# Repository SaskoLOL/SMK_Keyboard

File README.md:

# SMK_Keyboard
This is a cool 119 key mechanical keyboard. It has 9 macro keys, 4 on top and 5 on the left. (Total time spent: 40h)

#CAD
I modeled everything in fusion 360

This is the full case

It consist of 2 parts:

PCB
The schmetick consists of 119 switches and diodes and uses a rasbarry pi pico (orpheus pico)

The PCB consists only of 2 layers:

UPDATED PICTURE (because I had the thing mirrored and it looked like the screw holes would go trough the pcb and top case)

UPDATE: made the usb space look alot better:

Firmware:
The firmware was made in VS code with Pyhton

BOM:

119 cherry mx switches cost: 52.80€ Required: Yes Link: https://www.reichelt.at/at/de/shop/produkt/cherry_mx_blue_-_tastenmodul_-_fixierzapfen-369269?PROVID=2807&gad_source=1&gad_campaignid=21422869099&gbraid=0AAAAADwnxtat6u9lsAHToV6GKxf7BibTs&gclid=CjwKCAjwvuLDBhAOEiwAPtF0VhZ3tHRP4ssGiYqpavdrLBmLvci3DstJQDXffXF_gPWklEFFPWfM4RoCDl0QAvD_BwE 

One orpheus pico: 10€ Required: No

M3x16mm screws (6x): 3€: Required: No

119 blank keycaps: 29,90 €: Required: Yes Link:https://www.caseking.de/ducky-blank-white-pbt-set-mda-profile-133-keycaps-ansi-us-layout-ansi-us-layout/GAKC-530.html?gad_source=1&gad_campaignid=21451873868&gbraid=0AAAAABRBl3rp2MxtPfOOeLMF1GxUSPO_i&gclid=CjwKCAjwvuLDBhAOEiwAPtF0Vpwwld4mDaxte3PK0Otz3Z-v6C9MTZain8aGXCld9Vo5LzLQT2UPhRoCZhEQAvD_BwE ALIEXPRESS LINK (updated): https://de.aliexpress.com/i/1005008530984427.html?gatewayAdapt=glo2deu Cost:21,07$

3d printing Filament: 20€ Required Yes

Pcb: / Required: Yes
Total cost: 130$

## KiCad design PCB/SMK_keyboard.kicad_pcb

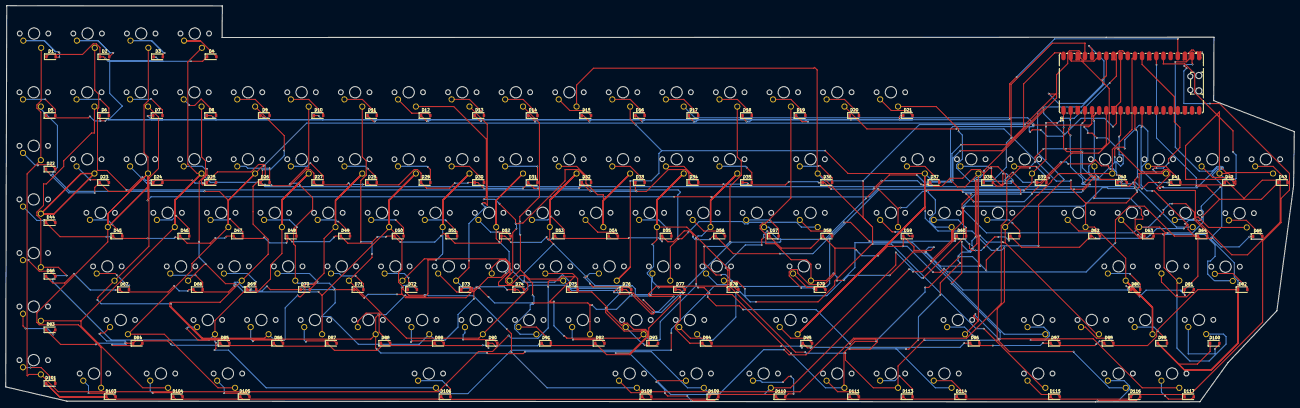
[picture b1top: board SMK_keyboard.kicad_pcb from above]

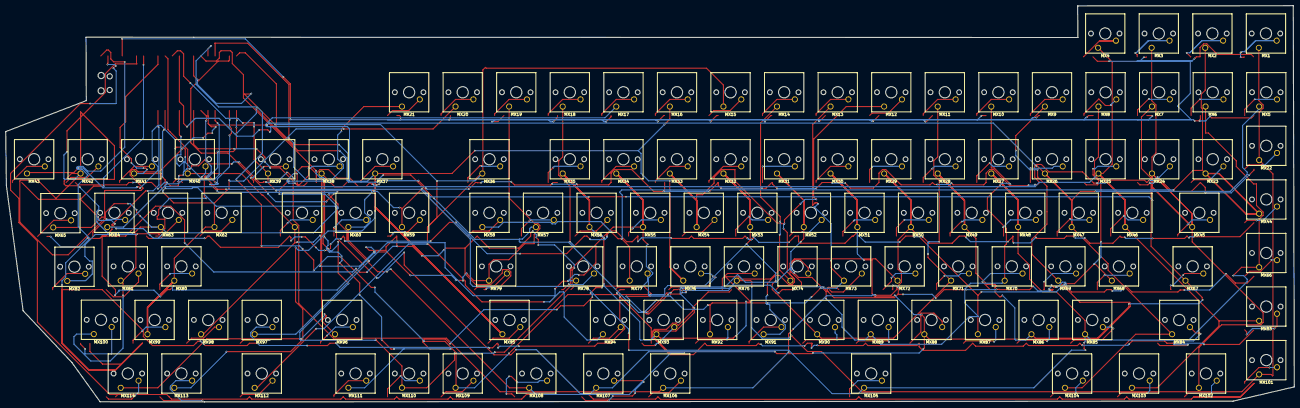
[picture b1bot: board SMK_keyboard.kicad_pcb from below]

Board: 2 copper layers, 458.2 x 140.9 mm, 229 parts (114 on the bottom side), 141 nets.

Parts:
D1, D2, D3, D4, D5, D6, D7, D8, D9, D10, D11, D12, D13, D14, D15, D16, D17, D18, D19, D20, D21, D22, D23, D24, D25, D26, D27, D28, D29, D30, D31, D32, D33, D34, D35, D36, D37, D38, D39, D40, D41, D42, D43, D44, D45, D46, D47, D48, D49, D50, D51, D52, D53, D54, D55, D56, D57, D58, D59, D60, D61, D62, D63, D64, D65, D66, D67, D68, D69, D70, D71, D72, D73, D74, D75, D76, D77, D78, D79, D80, D81, D82, D83, D84, D85, D86, D87, D88, D89, D90, D91, D92, D93, D94, D95, D96, D97, D98, D99, D100, D101, D103, D104, D105, D106, D108, D109, D110, D111, D113, D114, D115, D116, D117: D; D_SOD-123
MX1, MX2, MX3, MX4, MX5, MX6, MX7, MX8, MX9, MX10, MX11, MX12, MX13, MX14, MX15, MX16, MX17, MX18, MX19, MX20, MX21, MX22, MX23, MX24, MX25, MX26, MX27, MX28, MX29, MX30, MX31, MX32, MX33, MX34, MX35, MX36, MX37, MX38, MX39, MX40, MX41, MX42, MX43, MX44, MX45, MX46, MX47, MX48, MX49, MX50, MX51, MX52, MX53, MX54, MX55, MX56, MX57, MX58, MX59, MX60, MX61, MX62, MX63, MX64, MX65, MX66, MX67, MX68, MX69, MX70, MX71, MX72, MX73, MX74, MX75, MX76, MX77, MX78, MX79, MX80, MX81, MX82, MX83, MX84, MX85, MX86, MX87, MX88, MX89, MX90, MX91, MX92, MX93, MX94, MX95, MX96, MX97, MX98, MX99, MX100, MX101, MX102, MX103, MX104, MX105, MX106, MX107, MX108, MX109, MX110, MX111, MX112, MX113, MX114: MX_SW_HS; SW_Cherry_MX_1.00u_PCB
U1: Pico; RaspberryPi_Pico_Common_SMD

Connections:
unnamed: D1.2 (A), MX1.2
unnamed: D2.2 (A), MX2.2
unnamed: D3.2 (A), MX3.2
unnamed: D4.2 (A), MX4.2
unnamed: D5.2 (A), MX5.2
unnamed: D6.2 (A), MX6.2
unnamed: D7.2 (A), MX7.2
unnamed: D8.2 (A), MX8.2
unnamed: D9.2 (A), MX9.2
unnamed: D10.2 (A), MX10.2
unnamed: D11.2 (A), MX11.2
unnamed: D12.2 (A), MX12.2
unnamed: D13.2 (A), MX13.2
unnamed: D14.2 (A), MX14.2
unnamed: D15.2 (A), MX15.2
unnamed: D16.2 (A), MX16.2
unnamed: D17.2 (A), MX17.2
unnamed: D18.2 (A), MX18.2
unnamed: D19.2 (A), MX19.2
unnamed: D20.2 (A), MX20.2
unnamed: D21.2 (A), MX21.2
unnamed: D22.2 (A), MX22.2
unnamed: D23.2 (A), MX23.2
unnamed: D24.2 (A), MX24.2
unnamed: D25.2 (A), MX25.2
unnamed: D26.2 (A), MX26.2
unnamed: D27.2 (A), MX27.2
unnamed: D28.2 (A), MX28.2
unnamed: D29.2 (A), MX29.2
unnamed: D30.2 (A), MX30.2
unnamed: D31.2 (A), MX31.2
unnamed: D32.2 (A), MX32.2
unnamed: D33.2 (A), MX33.2
unnamed: D34.2 (A), MX34.2
unnamed: D35.2 (A), MX35.2
unnamed: D36.2 (A), MX36.2
unnamed: D37.2 (A), MX37.2
unnamed: D38.2 (A), MX38.2
unnamed: D39.2 (A), MX39.2
unnamed: D40.2 (A), MX40.2
unnamed: D41.2 (A), MX41.2
unnamed: D42.2 (A), MX42.2
unnamed: D43.2 (A), MX43.2
unnamed: D44.2 (A), MX44.2
unnamed: D45.2 (A), MX45.2
unnamed: D46.2 (A), MX46.2
unnamed: D47.2 (A), MX47.2
unnamed: D48.2 (A), MX48.2
unnamed: D49.2 (A), MX49.2
unnamed: D50.2 (A), MX50.2
unnamed: D51.2 (A), MX51.2
unnamed: D52.2 (A), MX52.2
unnamed: D53.2 (A), MX53.2
unnamed: D54.2 (A), MX54.2
unnamed: D55.2 (A), MX55.2
unnamed: D56.2 (A), MX56.2
unnamed: D57.2 (A), MX57.2
unnamed: D58.2 (A), MX58.2
unnamed: D59.2 (A), MX59.2
unnamed: D60.2 (A), MX60.2
unnamed: D61.2 (A), MX61.2
unnamed: D62.2 (A), MX62.2
unnamed: D63.2 (A), MX63.2
unnamed: D64.2 (A), MX64.2
unnamed: D65.2 (A), MX65.2
unnamed: D66.2 (A), MX66.2
unnamed: D67.2 (A), MX67.2
unnamed: D68.2 (A), MX68.2
unnamed: D69.2 (A), MX69.2
unnamed: D70.2 (A), MX70.2
unnamed: D71.2 (A), MX71.2
unnamed: D72.2 (A), MX72.2
unnamed: D73.2 (A), MX73.2
unnamed: D74.2 (A), MX74.2
unnamed: D75.2 (A), MX75.2
unnamed: D76.2 (A), MX76.2
unnamed: D77.2 (A), MX77.2
unnamed: D78.2 (A), MX78.2
unnamed: D79.2 (A), MX79.2
unnamed: D80.2 (A), MX80.2
unnamed: D81.2 (A), MX81.2
unnamed: D82.2 (A), MX82.2
unnamed: D83.2 (A), MX83.2
unnamed: D84.2 (A), MX84.2
unnamed: D85.2 (A), MX85.2
unnamed: D86.2 (A), MX86.2
unnamed: D87.2 (A), MX87.2
unnamed: D88.2 (A), MX88.2
unnamed: D89.2 (A), MX89.2
unnamed: D90.2 (A), MX90.2
unnamed: D91.2 (A), MX91.2
unnamed: D92.2 (A), MX92.2
unnamed: D93.2 (A), MX93.2
unnamed: D94.2 (A), MX94.2
unnamed: D95.2 (A), MX95.2
unnamed: D96.2 (A), MX96.2
unnamed: D97.2 (A), MX97.2
unnamed: D98.2 (A), MX98.2
unnamed: D99.2 (A), MX99.2
unnamed: D100.2 (A), MX100.2
unnamed: D101.2 (A), MX101.2
unnamed: D103.2 (A), MX102.2
unnamed: D104.2 (A), MX103.2
unnamed: D105.2 (A), MX104.2
unnamed: D106.2 (A), MX105.2
unnamed: D108.2 (A), MX106.2
unnamed: D109.2 (A), MX107.2
unnamed: D110.2 (A), MX108.2
unnamed: D111.2 (A), MX109.2
unnamed: D113.2 (A), MX110.2
unnamed: D114.2 (A), MX111.2
unnamed: D115.2 (A), MX112.2
unnamed: D116.2 (A), MX113.2
unnamed: D117.2 (A), MX114.2
unnamed: MX2.1, MX23.1, MX44.1, MX58.1, MX77.1
unnamed: MX12.1, MX33.1, MX54.1, MX72.1, MX91.1
unnamed: MX7.1, MX28.1, MX49.1, MX67.1, MX86.1
Row1: D75.1 (K), D77.1 (K), D82.1 (K), D83.1 (K), D84.1 (K), D85.1 (K), D86.1 (K), D87.1 (K), D88.1 (K), D89.1 (K), D90.1 (K), D91.1 (K), D92.1 (K), D93.1 (K), D94.1 (K), D95.1 (K), D96.1 (K), D97.1 (K), D98.1 (K), D99.1 (K), D100.1 (K), U1.1 (GPIO0)
Row2: D101.1 (K), D103.1 (K), D104.1 (K), D105.1 (K), D106.1 (K), D108.1 (K), D109.1 (K), D110.1 (K), D111.1 (K), D113.1 (K), D114.1 (K), D115.1 (K), D116.1 (K), D117.1 (K), U1.2 (GPIO1)
Row3: D1.1 (K), D2.1 (K), D3.1 (K), D4.1 (K), D5.1 (K), D6.1 (K), D7.1 (K), D8.1 (K), D9.1 (K), D10.1 (K), D11.1 (K), D12.1 (K), D13.1 (K), D14.1 (K), D15.1 (K), D16.1 (K), D17.1 (K), D18.1 (K), D19.1 (K), D20.1 (K), D21.1 (K), U1.4 (GPIO2)
Row4: D22.1 (K), D23.1 (K), D24.1 (K), D25.1 (K), D26.1 (K), D27.1 (K), D28.1 (K), D29.1 (K), D30.1 (K), D31.1 (K), D32.1 (K), D33.1 (K), D34.1 (K), D35.1 (K), D36.1 (K), D37.1 (K), D38.1 (K), D39.1 (K), D40.1 (K), D41.1 (K), D42.1 (K), U1.29 (GPIO22)
Row5: D43.1 (K), D44.1 (K), D45.1 (K), D46.1 (K), D47.1 (K), D48.1 (K), D49.1 (K), D50.1 (K), D51.1 (K), D52.1 (K), D53.1 (K), D54.1 (K), D55.1 (K), D56.1 (K), D60.1 (K), D61.1 (K), D62.1 (K), D63.1 (K), U1.7 (GPIO5)
Row6: D57.1 (K), D58.1 (K), D59.1 (K), D64.1 (K), D65.1 (K), D66.1 (K), D67.1 (K), D68.1 (K), D69.1 (K), D70.1 (K), D71.1 (K), D72.1 (K), D73.1 (K), D74.1 (K), D76.1 (K), D78.1 (K), D79.1 (K), D80.1 (K), D81.1 (K), U1.32 (GPIO27_ADC1)
col0: MX1.1, MX22.1, MX43.1, MX57.1, MX75.1, MX101.1, U1.21 (GPIO16)
col1: MX3.1, MX24.1, MX45.1, MX59.1, MX82.1, MX102.1, U1.22 (GPIO17)
col2: MX4.1, MX25.1, MX46.1, MX64.1, MX83.1, MX103.1, U1.24 (GPIO18)
col3: MX5.1, MX26.1, MX47.1, MX65.1, MX84.1, MX104.1, U1.25 (GPIO19)
col4: MX6.1, MX27.1, MX48.1, MX66.1, MX85.1, MX105.1, U1.26 (GPIO20)
col5: MX8.1, MX29.1, MX50.1, MX68.1, MX87.1, MX106.1, U1.27 (GPIO21)
col6: MX9.1, MX30.1, MX51.1, MX69.1, MX88.1, MX107.1, U1.31 (GPIO26_ADC0)
col7: MX10.1, MX31.1, MX52.1, MX70.1, MX89.1, MX108.1, U1.19 (GPIO14)
col8: MX11.1, MX32.1, MX53.1, MX71.1, MX90.1, MX109.1, U1.16 (GPIO12)
col9: MX13.1, MX34.1, MX55.1, MX73.1, MX92.1, MX110.1, U1.17 (GPIO13)
col10: MX14.1, MX35.1, MX56.1, MX74.1, MX93.1, MX111.1, U1.15 (GPIO11)
col11: MX15.1, MX36.1, MX94.1, MX112.1, U1.14 (GPIO10)
col12: MX16.1, MX37.1, MX76.1, MX95.1, MX113.1, U1.20 (GPIO15)
col13: MX17.1, MX38.1, MX96.1, MX114.1, U1.12 (GPIO9)
col14: MX18.1, MX39.1, MX60.1, MX78.1, MX97.1, U1.11 (GPIO8)
col15: MX19.1, MX40.1, MX61.1, MX79.1, MX98.1, U1.10 (GPIO7)
col16: MX20.1, MX41.1, MX62.1, MX80.1, MX99.1, U1.9 (GPIO6)
col17: MX21.1, MX42.1, MX63.1, MX81.1, MX100.1, U1.6 (GPIO4)

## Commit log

2025-07-17 Create ignore
